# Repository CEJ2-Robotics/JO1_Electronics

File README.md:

# John Deere Tractor Navigation System - Electronics

<p align="justify"> This repository contains the PCB layout for a <strong>shield-style board</strong> designed to interface with the <i>NUCLEO-H745ZI-Q</i> development board. The PCB integrates various components and connection interfaces required for the tractor navigation system developed in collaboration with John Deere, serving as a practical application of embedded systems concepts. The implementation details of this electronics design can be found in the <a href="https://github.com/CEJ2-Robotics/JO1_Embedded">embedded software repository</a>.</p>

## System Overview

<p align="justify">The custom PCB serves as a connection hub for the system's components, handling:</p>

<ul>
  <li><strong>Power distribution</strong> to components</li>
  <li><strong>CAN interface (FDCAN1)</strong> for encoder data</li>
  <li><strong>I2C connection (I2C4)</strong> for the MPU6050 IMU</li>
  <li><strong>SPI interface (SPI5)</strong> for the nRF24L01 wireless module</li>
  <li><strong>PWM signal routing (TIM13, TIM14, TIM1)</strong> for motors and buzzer</li>
</ul>

## Power Distribution

<p align="justify">The PCB design includes three power input screw terminals. Here's our implementation from the embedded repository:</p>

### Logic Power Screw Terminals

<ul>
  <li><strong>5V terminal:</strong> Connected to external LM2596 regulator outputting 5V</li>
  <li><strong>3.3V terminal:</strong> Connected to external LM2596 regulator outputting 3.3V</li>
  <li>Both regulators were powered by 7.4V from two <strong>3.7V Li-Po cells</strong> in series</li>
</ul>

### STM32 Power Screw Terminal

<ul>
  <li><strong>7.4V terminal:</strong> Connects directly to NUCLEO-H745ZI-Q's VIN</li>
  <li><strong>Board configuration:</strong> JP2 jumper on pins 3-4</li>
  <li><strong>Power specifications:</strong>
    <ul>
      <li><strong>Input range:</strong> 7-11V</li>
      <li><strong>Current draw varies with voltage:</strong></li>
      <ul>
        <li>800mA @ 7V</li>
        <li>450mA @ 7-9V</li>
        <li>250mA @ 9-11V</li>
      </ul>
    </ul>
  </li>
</ul>

### ESC and STM32 Connection

<ul>
  <li>The <strong>ESC</strong> is a separate pre-built circuit with its own power connections and is not powered through the PCB.</li>
  <li>In our setup, we used a <strong>7.4V Li-Po 2S battery</strong> to power both:
    <ul>
      <li>The <strong>ESC</strong> directly</li>
      <li>The <strong>STM32</strong> through the PCB's 7.4V screw terminal</li>
    </ul>
  </li>
</ul>

## Schematic Diagram & Component List

| Component          | Specifications              | Purpose                   | Location               |
|------------------- |---------------------------- |-------------------------- |----------------------- |
| NUCLEO-H745ZI-Q    | Dual-core ARM Cortex-M7/M4  | Main controller           | Shield base board      |
| Arduino Nano       | ATmega328P                  | Encoder preprocessing     | On shield PCB          |
| nRF24L01           | 2.4GHz wireless module      | GPS data reception        | On shield PCB          |
| MPU6050            | 6-DOF IMU                   | Orientation tracking      | On shield PCB          |
| GM 25-370          | 12V DC motor with encoder   | Drive system              | External (pins on PCB) |
| MCP2515            | CAN controller              | CAN-SPI interface         | On shield PCB          |
| TJA1051            | CAN transceiver             | CAN physical layer        | On shield PCB          |
| MG996R             | Servo motor                 | Steering control          | External (pins on PCB) | 
| 30A ESC            | Electronic speed controller | Motor drive control       | External (pins on PCB) |
| HW-508             | Passive buzzer              | Audio feedback            | On shield PCB          |
| LM2596 (x2)        | DC-DC Step Down             | 5V and 3.3V regulation    | External (recommended) |

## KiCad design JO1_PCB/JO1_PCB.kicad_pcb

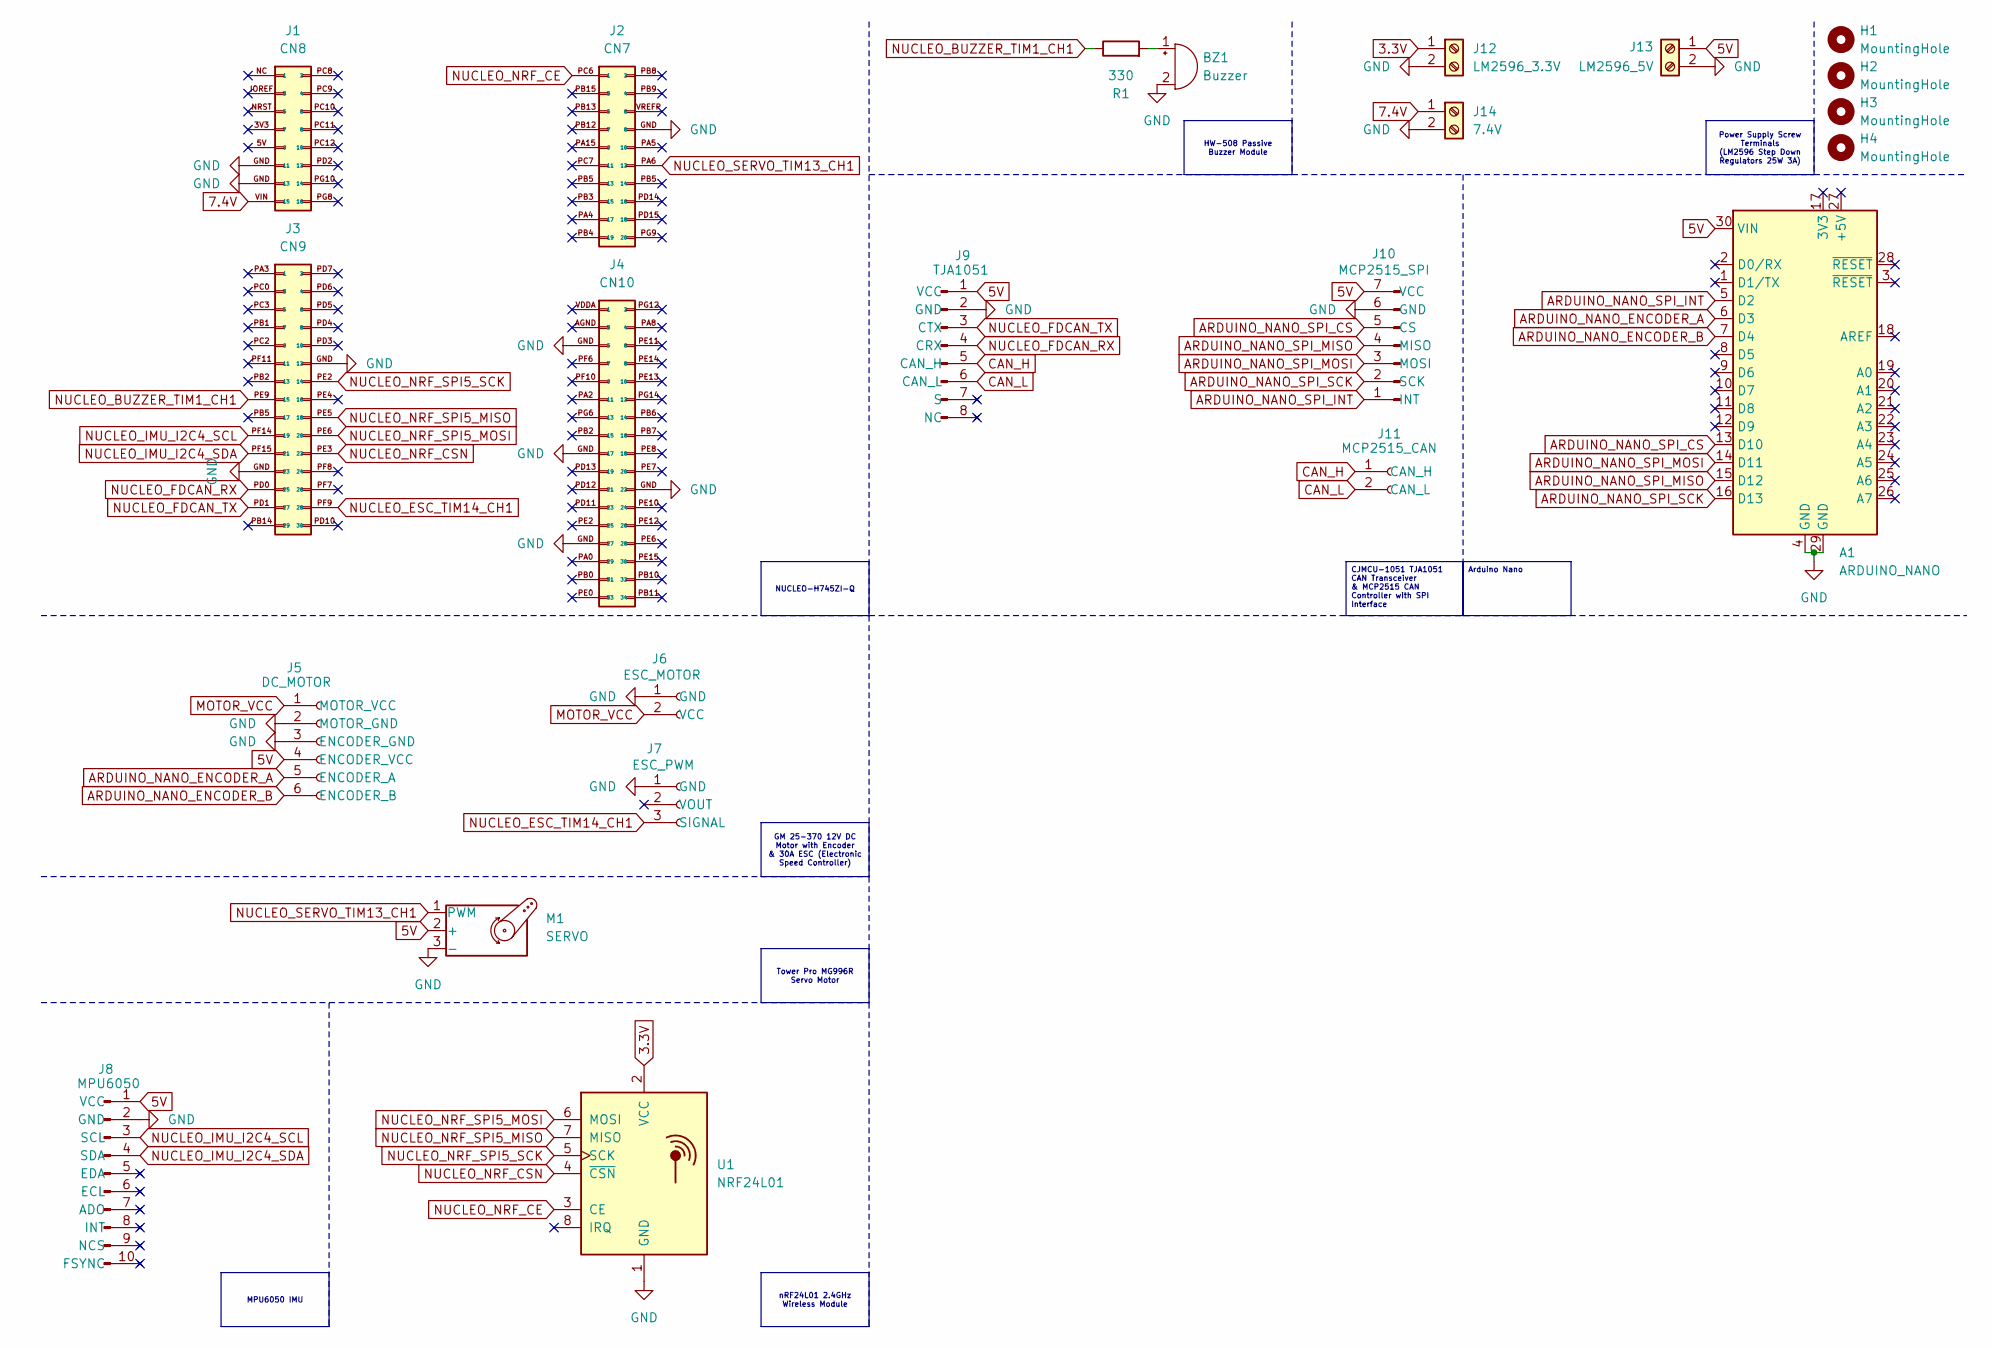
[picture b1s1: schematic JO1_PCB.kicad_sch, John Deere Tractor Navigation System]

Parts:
A1: ARDUINO_NANO; Arduino_Nano
BZ1: Buzzer; Buzzer_12x9.5RM7.6
H1, H2, H3, H4: MountingHole; MountingHole_2.1mm
J1: CN8; PinHeader_2x08_P2.54mm_Vertical
J2: CN7; PinHeader_2x10_P2.54mm_Vertical
J3: CN9; PinHeader_2x15_P2.54mm_Vertical
J4: CN10; PinHeader_2x17_P2.54mm_Vertical
J5: DC_MOTOR; PinHeader_1x06_P2.54mm_Vertical
J6: ESC_MOTOR; PinHeader_1x02_P2.54mm_Vertical
J7: ESC_PWM; PinHeader_1x03_P2.54mm_Vertical
J8: MPU6050; PinSocket_1x10_P2.54mm_Vertical
J9: TJA1051; PinSocket_1x08_P2.54mm_Vertical
J10: MCP2515_SPI; PinSocket_1x07_P2.54mm_Vertical
J11: MCP2515_CAN; PinHeader_1x02_P2.54mm_Vertical
J12: LM2596_3.3V; TerminalBlock_MetzConnect_Type094_RT03502HBLU_1x02_P5.00mm_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
J13: LM2596_5V; TerminalBlock_MetzConnect_Type094_RT03502HBLU_1x02_P5.00mm_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
J14: 7.4V; TerminalBlock_MetzConnect_Type094_RT03502HBLU_1x02_P5.00mm_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
M1: SERVO; PinHeader_1x03_P2.54mm_Vertical
R1: 330; R_Axial_DIN0207_L6.3mm_D2.5mm_P7.62mm_Horizontal
U1: NRF24L01; nRF24L01_Breakout

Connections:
3.3V: J12.1, U1.2 (VCC)
5V: A1.30 (VIN), J5.4 (ENCODER_VCC), J8.1 (VCC), J9.1 (VCC), J10.7 (VCC), J13.1, M1.2 (+)
7.4V: J1.VIN (15), J14.1
ARDUINO_NANO_ENCODER_A: A1.6 (D3), J5.5 (ENCODER_A)
ARDUINO_NANO_ENCODER_B: A1.7 (D4), J5.6 (ENCODER_B)
ARDUINO_NANO_SPI_CS: A1.13 (D10), J10.5 (CS)
ARDUINO_NANO_SPI_INT: A1.5 (D2), J10.1 (INT)
ARDUINO_NANO_SPI_MISO: A1.15 (D12), J10.4 (MISO)
ARDUINO_NANO_SPI_MOSI: A1.14 (D11), J10.3 (MOSI)
ARDUINO_NANO_SPI_SCK: A1.16 (D13), J10.2 (SCK)
CAN_H: J9.5 (CAN_H), J11.1 (CAN_H)
CAN_L: J9.6 (CAN_L), J11.2 (CAN_L)
GND: A1.4 (GND), A1.29 (GND), BZ1.2 (-), J1.GND (11), J2.GND (8), J3.GND (23), J4.GND (5), J5.2 (MOTOR_GND), J5.3 (ENCODER_GND), J6.1 (GND), J7.1 (GND), J8.2 (GND), J9.2 (GND), J10.6 (GND), J12.2, J13.2, J14.2, M1.3 (-), U1.1 (GND)
MOTOR_VCC: J5.1 (MOTOR_VCC), J6.2 (VCC)
NUCLEO_BUZZER_TIM1_CH1: J3.PE9 (15), R1.1
NUCLEO_ESC_TIM14_CH1: J3.PF9 (28), J7.3 (SIGNAL)
NUCLEO_FDCAN_RX: J3.PD0 (25), J9.4 (CRX)
NUCLEO_FDCAN_TX: J3.PD1 (27), J9.3 (CTX)
NUCLEO_IMU_I2C4_SCL: J3.PF14 (19), J8.3 (SCL)
NUCLEO_IMU_I2C4_SDA: J3.PF15 (21), J8.4 (SDA)
NUCLEO_NRF_CE: J2.PC6 (1), U1.3 (CE)
NUCLEO_NRF_CSN: J3.PE3 (22), U1.4 (~CSN)
NUCLEO_NRF_SPI5_MISO: J3.PE5 (18), U1.7 (MISO)
NUCLEO_NRF_SPI5_MOSI: J3.PE6 (20), U1.6 (MOSI)
NUCLEO_NRF_SPI5_SCK: J3.PE2 (14), U1.5 (SCK)
NUCLEO_SERVO_TIM13_CH1: J2.PA6 (12), M1.1 (PWM)
unnamed: BZ1.1 (+), R1.2

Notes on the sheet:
HW-508 Passive Buzzer Module
GM 25-370 12V DC Motor with Encoder & 30A ESC (Electronic Speed Controller)
Tower Pro MG996R Servo Motor
nRF24L01 2.4GHz Wireless Module
MPU6050 IMU
Power Supply Screw Terminals (LM2596 Step Down Regulators 25W 3A)
Arduino Nano
NUCLEO-H745ZI-Q
CJMCU-1051 TJA1051 CAN Transceiver & MCP2515 CAN Controller with SPI Interface

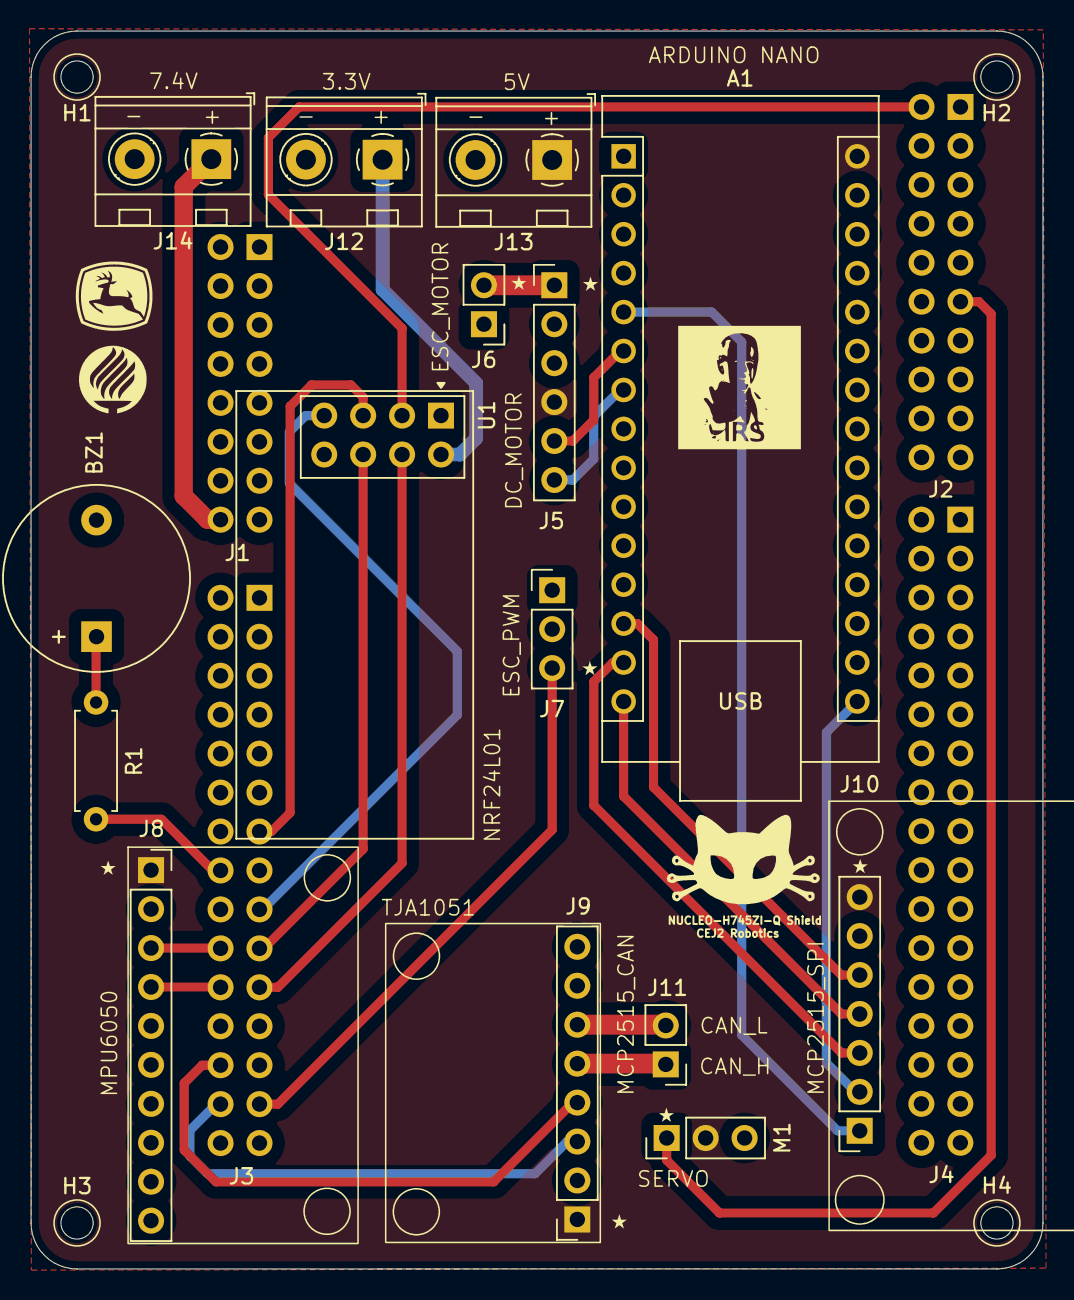
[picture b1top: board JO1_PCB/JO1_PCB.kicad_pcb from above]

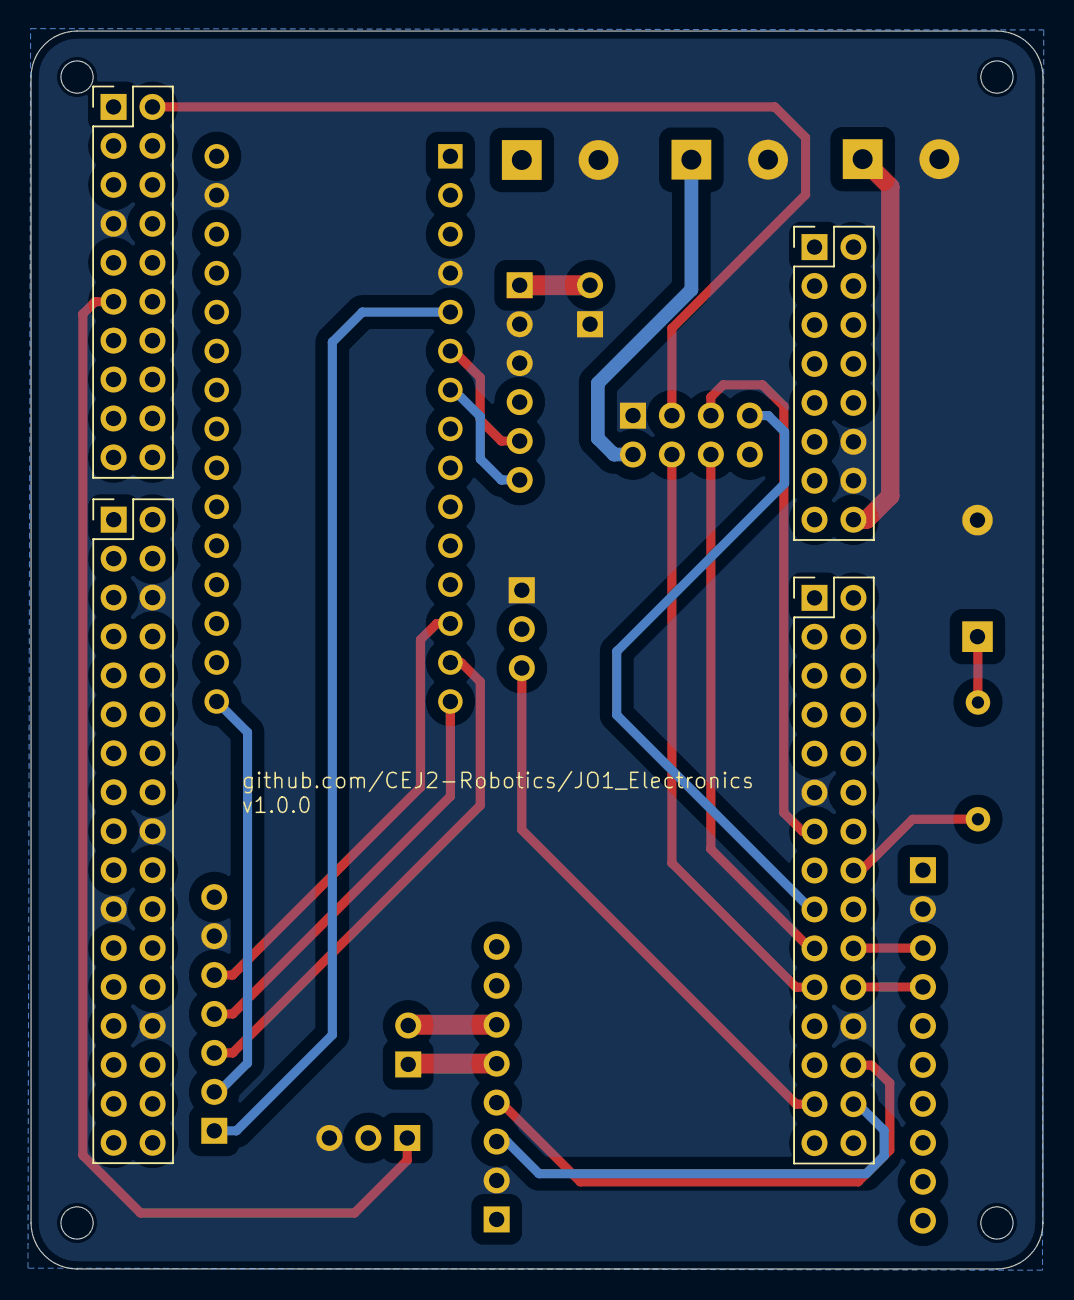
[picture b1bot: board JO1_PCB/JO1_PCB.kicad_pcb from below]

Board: 2 copper layers, 66.0 x 80.7 mm, 23 parts (4 on the bottom side), 27 nets.

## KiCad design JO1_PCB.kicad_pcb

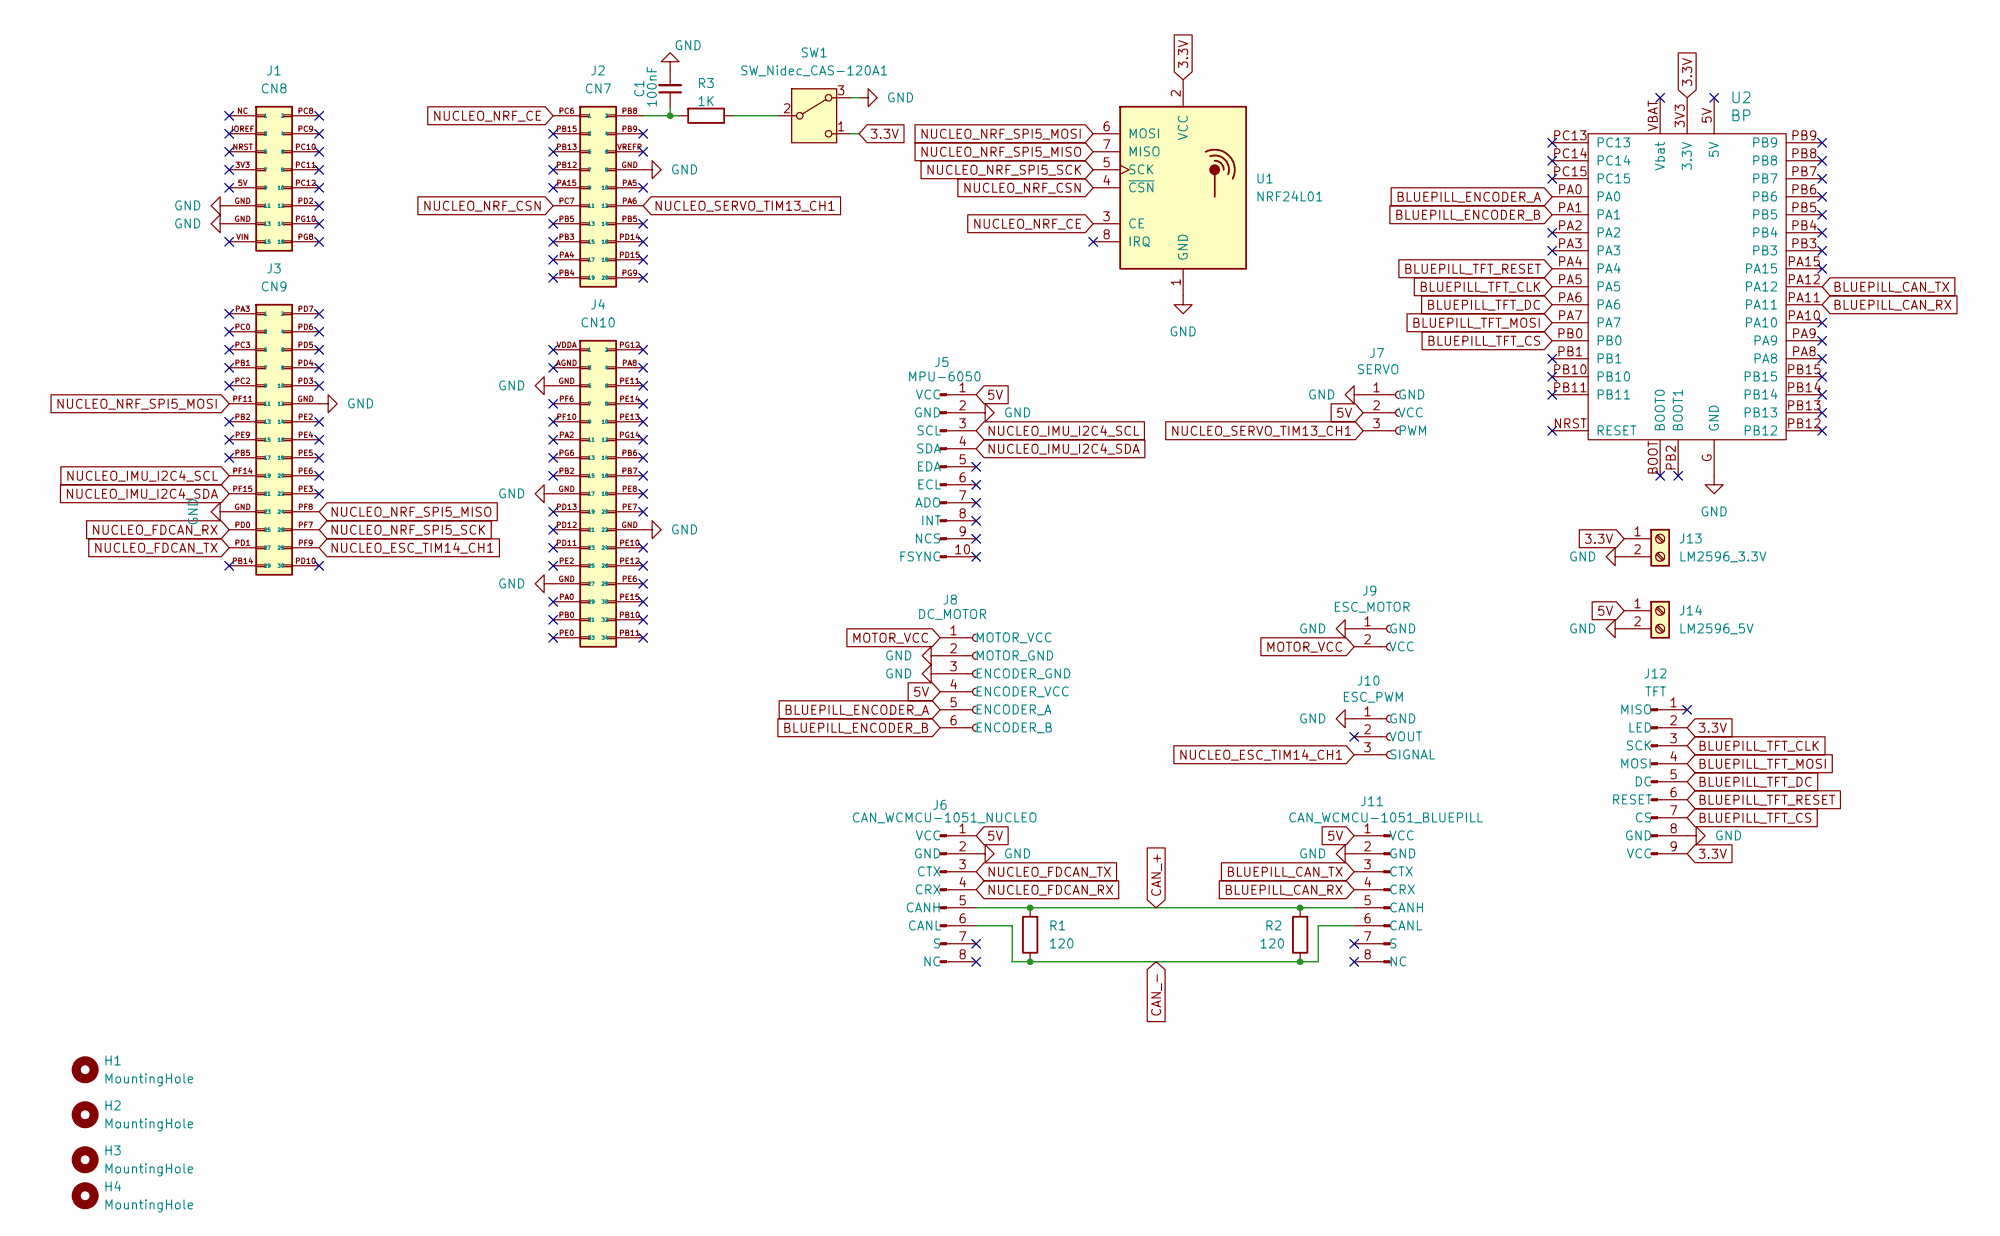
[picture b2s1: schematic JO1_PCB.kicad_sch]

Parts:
C1: 100nF; C_Disc_D4.7mm_W2.5mm_P5.00mm
H1, H2, H3, H4: MountingHole; MountingHole_2.1mm
J1: CN8; PinHeader_2x08_P2.54mm_Vertical
J2: CN7; PinHeader_2x10_P2.54mm_Vertical
J3: CN9; PinHeader_2x15_P2.54mm_Vertical
J4: CN10; PinHeader_2x17_P2.54mm_Vertical
J5: MPU-6050; PinSocket_1x10_P2.54mm_Vertical
J6: CAN_WCMCU-1051_NUCLEO; PinSocket_1x08_P2.54mm_Vertical
J7: SERVO; PinHeader_1x03_P2.54mm_Vertical
J8: DC_MOTOR; PinHeader_1x06_P2.54mm_Vertical
J9: ESC_MOTOR; PinHeader_1x02_P2.54mm_Vertical
J10: ESC_PWM; PinHeader_1x03_P2.54mm_Vertical
J11: CAN_WCMCU-1051_BLUEPILL; PinSocket_1x08_P2.54mm_Vertical
J12: TFT; PinSocket_1x09_P2.54mm_Vertical
J13: LM2596_3.3V; TerminalBlock_MetzConnect_Type094_RT03502HBLU_1x02_P5.00mm_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
J14: LM2596_5V; TerminalBlock_MetzConnect_Type094_RT03502HBLU_1x02_P5.00mm_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
R1, R2: 120; R_Axial_DIN0207_L6.3mm_D2.5mm_P10.16mm_Horizontal
R3: 1K; R_Axial_DIN0207_L6.3mm_D2.5mm_P10.16mm_Horizontal
SW1: SW_Nidec_CAS-120A1; SW_Slide-03_Wuerth-WS-SLTV_10x2.5x6.4_P2.54mm
U1: NRF24L01; nRF24L01_Breakout
U2: BP; blue_pill

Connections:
3.3V: J12.2 (LED), J12.9 (VCC), J13.1, SW1.1 (C), U1.2 (VCC), U2.3V3 (3.3V)
5V: J5.1 (VCC), J6.1 (VCC), J7.2 (VCC), J8.4 (ENCODER_VCC), J11.1 (VCC), J14.1
BLUEPILL_CAN_RX: J11.4 (CRX), U2.PA11
BLUEPILL_CAN_TX: J11.3 (CTX), U2.PA12
BLUEPILL_ENCODER_A: J8.5 (ENCODER_A), U2.PA0
BLUEPILL_ENCODER_B: J8.6 (ENCODER_B), U2.PA1
BLUEPILL_TFT_CLK: J12.3 (SCK), U2.PA5
BLUEPILL_TFT_CS: J12.7 (CS), U2.PB0
BLUEPILL_TFT_DC: J12.5 (DC), U2.PA6
BLUEPILL_TFT_MOSI: J12.4 (MOSI), U2.PA7
BLUEPILL_TFT_RESET: J12.6 (RESET), U2.PA4
CAN_+: J6.5 (CANH), J11.5 (CANH), R1.2, R2.2
CAN_-: J6.6 (CANL), J11.6 (CANL), R1.1, R2.1
GND: C1.2, J1.GND (11), J2.GND (8), J3.GND (23), J4.GND (5), J5.2 (GND), J6.2 (GND), J7.1 (GND), J8.2 (MOTOR_GND), J8.3 (ENCODER_GND), J9.1 (GND), J10.1 (GND), J11.2 (GND), J12.8 (GND), J13.2, J14.2, SW1.3 (A), U1.1 (GND), U2.G (GND)
MOTOR_VCC: J8.1 (MOTOR_VCC), J9.2 (VCC)
NUCLEO_ESC_TIM14_CH1: J3.PF9 (28), J10.3 (SIGNAL)
NUCLEO_FDCAN_RX: J3.PD0 (25), J6.4 (CRX)
NUCLEO_FDCAN_TX: J3.PD1 (27), J6.3 (CTX)
NUCLEO_IMU_I2C4_SCL: J3.PF14 (19), J5.3 (SCL)
NUCLEO_IMU_I2C4_SDA: J3.PF15 (21), J5.4 (SDA)
NUCLEO_NRF_CE: J2.PC6 (1), U1.3 (CE)
NUCLEO_NRF_CSN: J2.PC7 (11), U1.4 (~CSN)
NUCLEO_NRF_SPI5_MISO: J3.PF8 (24), U1.7 (MISO)
NUCLEO_NRF_SPI5_MOSI: J3.PF11 (11), U1.6 (MOSI)
NUCLEO_NRF_SPI5_SCK: J3.PF7 (26), U1.5 (SCK)
NUCLEO_SERVO_TIM13_CH1: J2.PA6 (12), J7.3 (PWM)
unnamed: C1.1, J2.PB8 (2), R3.2
unnamed: R3.1, SW1.2 (B)

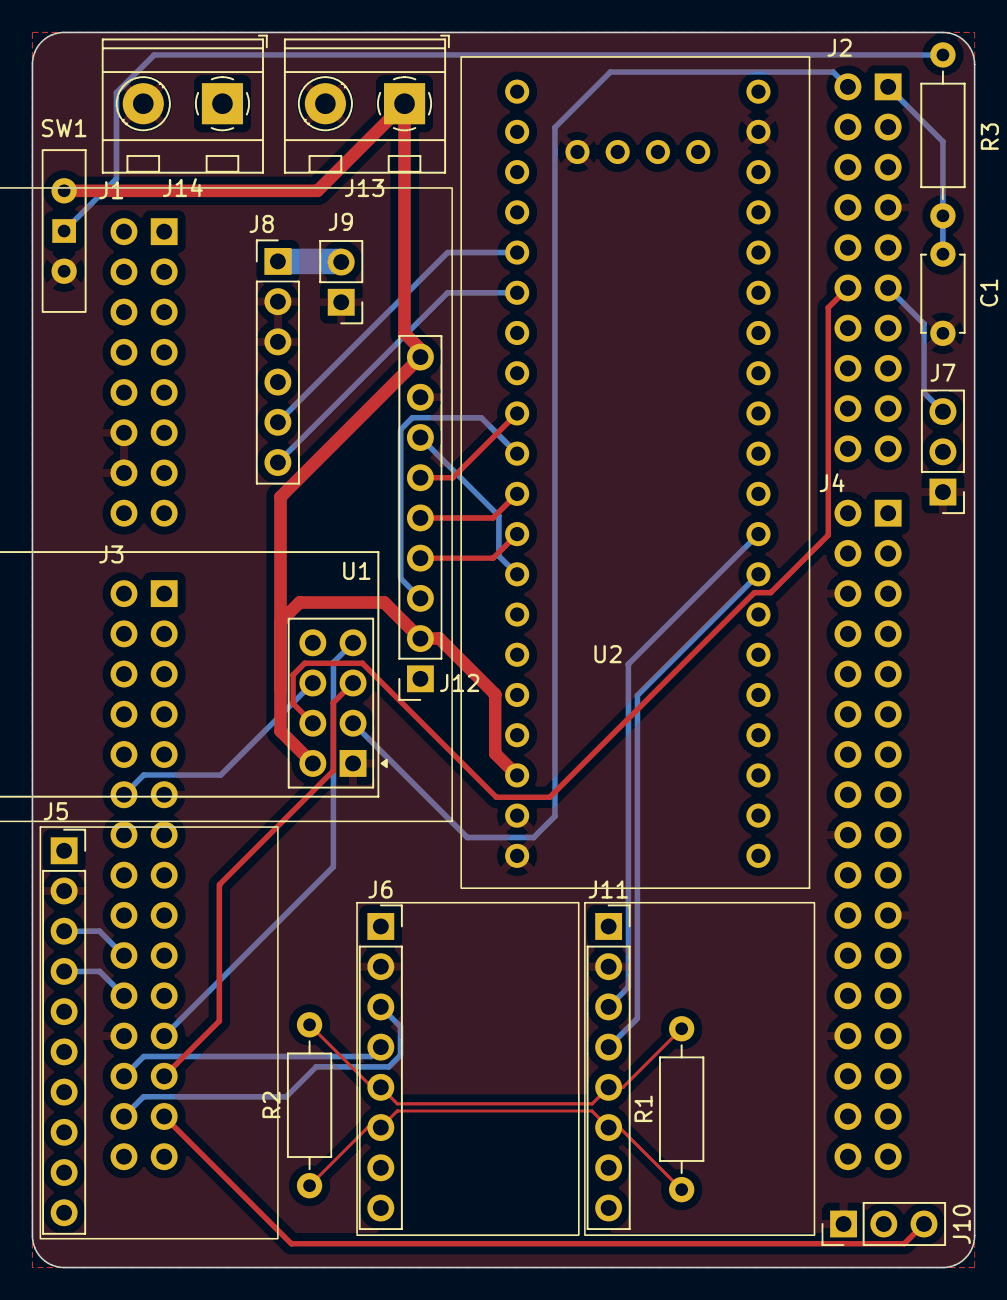
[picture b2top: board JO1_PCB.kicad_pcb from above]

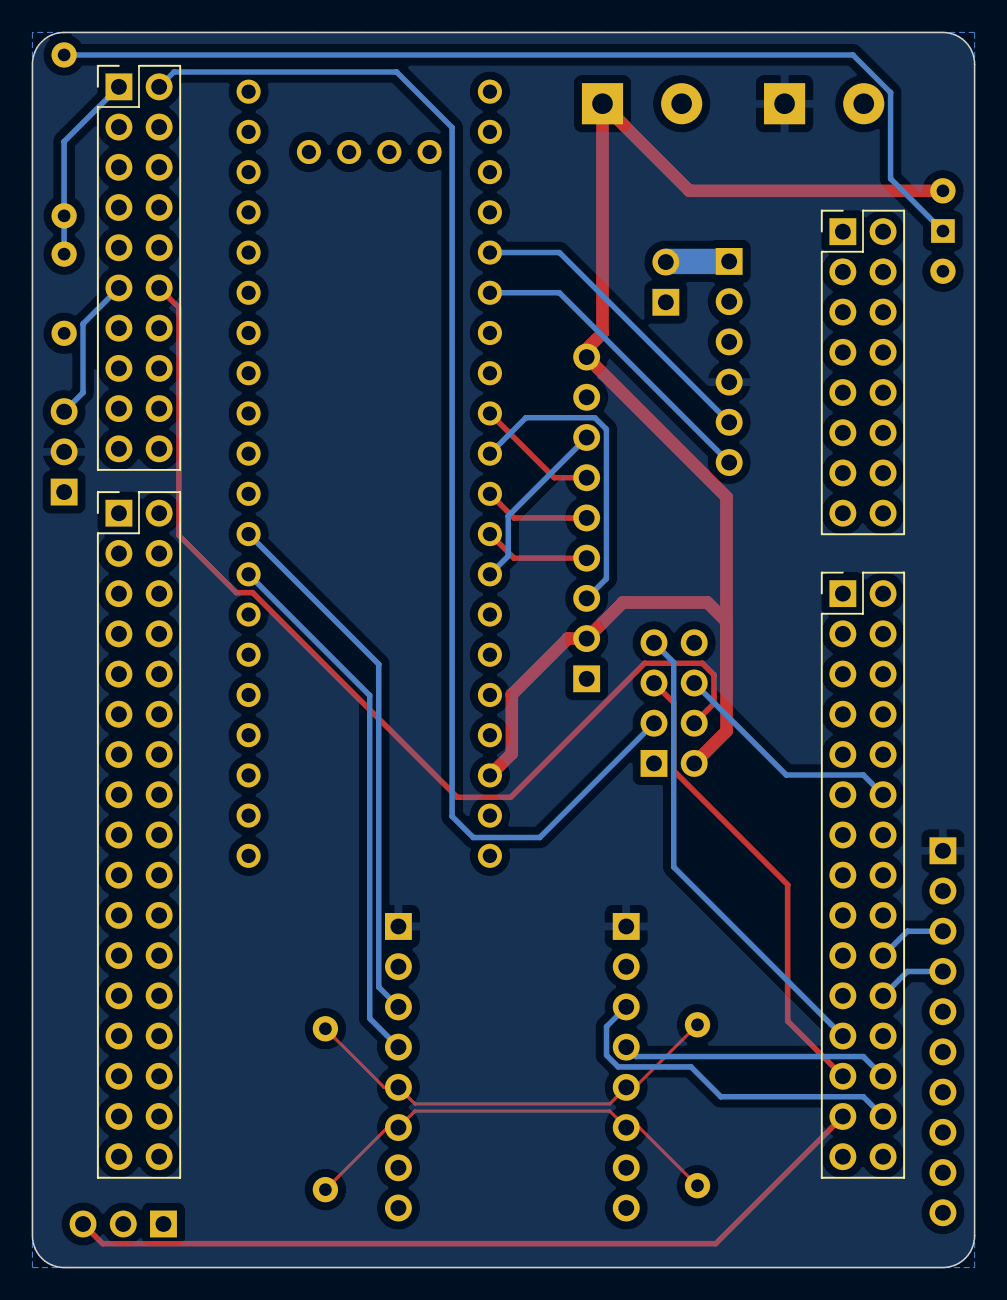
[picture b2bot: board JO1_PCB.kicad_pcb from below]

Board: 2 copper layers, 59.5 x 78.0 mm, 25 parts (4 on the bottom side), 28 nets.

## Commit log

2024-11-13 MPU-6050 symbol and footprint
2024-11-13 CN7 header done
2024-11-13 CN8 and CN9 header names and numbers
2024-11-13 Header CN10 done
2024-11-15 reborn
2024-11-15 Corrected connectors
2024-11-15 Added several components to the schematic
2024-11-15 avances.........
2024-11-16 Modified global label
2024-11-18 Added CAN transceiver for Blue Pill
2024-11-18 Placed components
2024-11-18 Added screw terminals
2024-11-20 Corrected CAN bus
2024-11-21 Routing
2024-11-21 ya mero casi
2024-11-21 new fenolica
2024-11-22 Version Nov 21
2024-11-22 Removed trace route that could potentially disrupt the PCB's functionality
2024-11-22 Final revision
2024-11-25 Modified SPI
2024-12-27 Final revision without routing
2024-12-27 .gitignore applied
2024-12-27 Routed PCB
2025-01-11 Added visual indications
2025-01-12 Added text
